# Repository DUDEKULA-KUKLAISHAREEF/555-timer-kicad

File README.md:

# 555-timer-kicad
This project presents a 555 Timer circuit designed using KiCad for pulse generation and timing applications. The design includes schematic creation, PCB layout, component placement, and routing. The circuit is compact, fabrication-ready, and suitable for learning electronics, PCB design, and embedded hardware development.

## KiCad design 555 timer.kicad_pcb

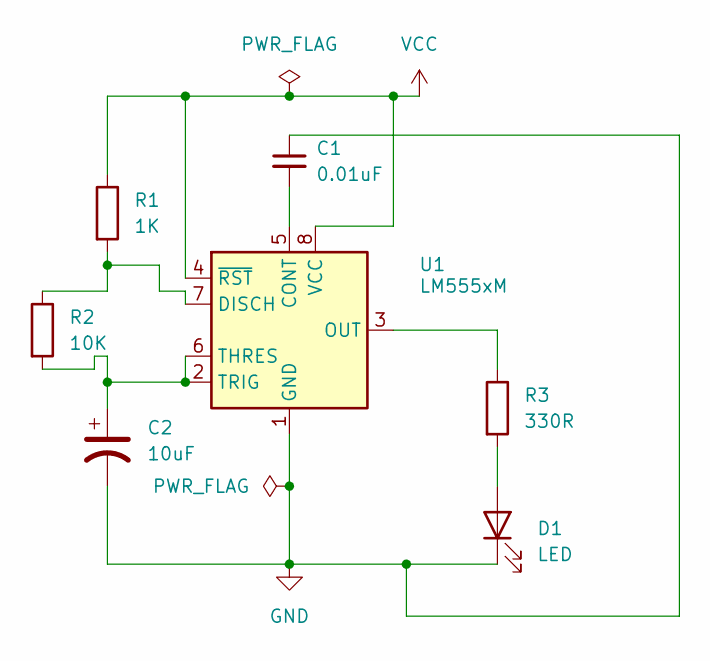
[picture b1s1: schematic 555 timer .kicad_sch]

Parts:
C1: 0.01uF; CP_Radial_D4.0mm_P1.50mm
C2: 10uF; C_Disc_D3.0mm_W1.6mm_P2.50mm
D1: LED; LED_D1.8mm_W1.8mm_H2.4mm_Horizontal_O1.27mm_Z1.6mm
R1: 1K; R_Axial_DIN0204_L3.6mm_D1.6mm_P1.90mm_Vertical
R2: 10K; R_Axial_DIN0204_L3.6mm_D1.6mm_P2.54mm_Vertical
R3: 330R; R_Axial_DIN0204_L3.6mm_D1.6mm_P5.08mm_Horizontal
U1: LM555xM; SOIC-8_3.9x4.9mm_P1.27mm

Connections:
GND: C1.1, C2.2, D1.1 (K), U1.1 (GND)
unnamed: D1.2 (A), R3.2
unnamed: C1.2, U1.5 (CONT)
unnamed: R1.2, R2.1, U1.7 (DISCH)
unnamed: R3.1, U1.3 (OUT)
unnamed: C2.1, R2.2, U1.2 (TRIG), U1.6 (THRES)
VCC: R1.1, U1.4 (~RST), U1.8 (VCC)

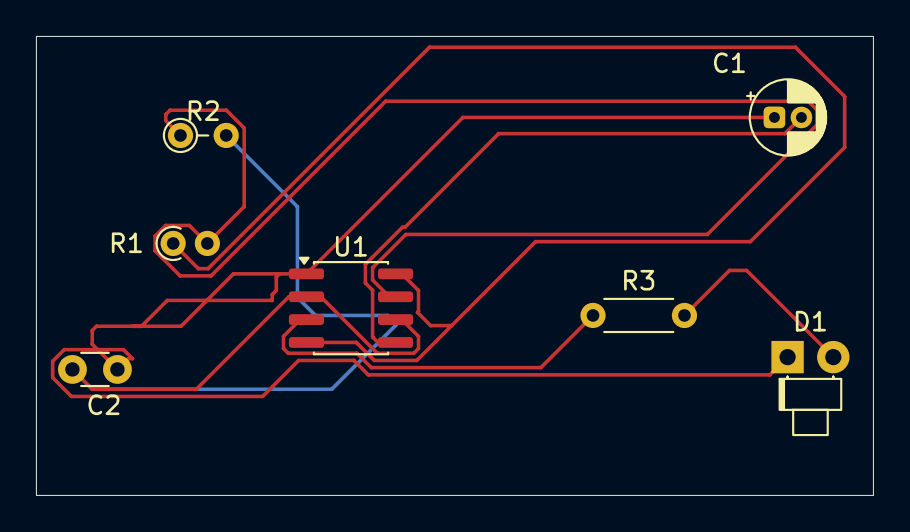
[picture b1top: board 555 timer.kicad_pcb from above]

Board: 2 copper layers, 46.5 x 25.5 mm, 7 parts (0 on the bottom side), 7 nets.
